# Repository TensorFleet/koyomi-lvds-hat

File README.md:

# Project Koyomi - display testing hat

This is the first part of the development of Project Koyomi, read [this blog post](https://blog.exentio.sexy/2023/12/11/project-koyomi-planning.html)
for more.  
The purpose of this Raspberry Pi hat is to test and play around with the
display of the Vaio P before further development of the motherboard.  

The board is currently tested and working [as shown here](https://blog.exentio.sexy/2024/05/09/project-koyomi-update-3.html)!

The board uses Texas Instruments' SN75LVDS83B LVDS transmitter using the Pi's
DPI signals to send video out to the display. The final motherboard will use a
DVI receiver to free up the Raspberry's GPIO, a small converter board is in
development and [you can find it here](https://github.com/exentio/koyomi-hdmi-lvds).  

The display connector is made by I-PEX, and the model numbers are
`20374-030E-31`/`20374-R30E-31`, they're the same but the 0 variant seems to be
more common.  
The display, in my case a LT080EE04100 by Toshiba (it should be the same for
all Vaio Ps), has no backlight driver, and for that the backlight pins are
broken out, allowing testing of different drivers.  
The driver will be controlled using software I2C since all the hardware I2C
pins are already used by DPI. The assigned GPIOs are 23 for SDA and 24 for SCL.
More info about software I2C on [this page](https://learn.adafruit.com/raspberry-pi-i2c-clock-stretching-fixes/software-i2c).

The current settings used in `config.txt` (on top of the default) is:  
```
dtparam=i2c_arm=off
dtparam=spi=off
display_auto_detect=0
dtoverlay=vc4-kms-dpi-generic
dtparam=hactive=1600,hfp=32,hsync=65,hbp=97
dtparam=vactive=768,vfp=1,vsync=1,vbp=8
dtparam=width-mm=182,height-mm=87
dtparam=clock-frequency=83600000,rgb666
framebuffer_width=1600
framebuffer_height=768
dtoverlay=i2c-gpio,i2c_gpio_sda=23,i2c_gpio_scl=24
disable_overscan=1
```
---

Huge thanks to Arya ([@CRImier](https://github.com/CRImier)) for her help during most phases of the design!

---

## Note on this copy (TensorFleet)

This is a **modified copy** of [exentio/koyomi-lvds-hat](https://github.com/exentio/koyomi-lvds-hat),
redistributed under CERN-OHL-S-2.0. It exists because GitHub would not let us fork the upstream
repository (`403: You can't fork this repository at this time`), so we could not open a pull request.

**Modification made** (CERN-OHL-S-2.0 §3.3 requires modifications to be identified):

- `Add F.Mask to DLP2ADN121HL4L pads so FL1/FL2 are solderable` — the
  `Murata_DLP2ADN121HL4L` footprint declared its pads as `(layers "F.Cu" "F.Paste")` with no
  `"F.Mask"`, so no solder mask openings were generated for FL1/FL2 and all 16 pads were covered by
  solder mask. Fixed in the library footprint and in both placed instances. Exporting the F.Mask layer
  before and after gives 197 → 213 flashes: exactly 16 new openings, all at the FL1/FL2 pad
  coordinates, nothing else changed.

  Found when JLCPCB flagged it during production-file preparation for a batch of these boards. Note
  that KiCad's DRC does **not** check for missing solder mask openings, so this passes a clean DRC.

Everything else is unmodified upstream work by Exentio. `gerbers/` is upstream's snapshot and has
**not** been regenerated, so it still reflects the pre-fix state — regenerate from source before
fabricating.

Upstream author: if you're reading this, the fix is a two-line change and we'd happily send it as a PR
if forking becomes possible. Thanks for publishing the design.

## TensorFleet compact RGB variant

`variants/koyomi-lvds-hat-rgb-compact-r2.0/` is a fabrication-closed compact
fork of the tested RGB/DPI design. It replaces the 2×20 Raspberry Pi header
with the carrier's 40-contact FH41 FFC, consolidates the system connection into
one harness, and demonstrates a 65.0 × 28.25 mm half-area floorplan. See the
variant README for its exact status and routing gate.

`variants/koyomi-lvds-hat-rgb-compact-r2.1-single-side/` preserves that outline
and interface while moving every fitted SMD component to the front. It is the
single-side-assembly successor and remains fabrication-closed until routing and
release verification are complete.

`variants/koyomi-lvds-hat-rgb-compact-r2.2-backlight-ffc/` adds one keyed
12-contact FFC connector for the complete legacy J5/J6 LCD-backlight harness:
VCD1–VCD6, VAD, 5 V, ground, PWM, enable, and the preserved unused contact.
It remains a single-side, half-area floorplan and is still fabrication-closed
pending native routing and release verification.

`variants/koyomi-lvds-hat-rgb-compact-r2.6-production/` is the current compact
RGB fabrication candidate. It is fully routed, keeps all 23 fitted parts on the
top side, passes zero-error DRC/ERC and the routed interface audit, and restores
all panel-sideband and backlight endpoints through the consolidated cables. It
must be paired with CM5 carrier B2.2; see the variant README and the checksumed
`fab/r2.6-compact-rgb-production-jlc-candidate/` package before quoting.

`variants/koyomi-lvds-hat-rgb-compact-r2.7-30pct-floorplan/` is the immutable,
fully routed 58.0 × 22.2 mm-base successor. It reduces R2.6 PCB area by 29.33%,
retains all 23 fitted parts on the top side, and passes DRC, ERC, routed-interface,
interconnect, and edge-orientation release gates.

`variants/koyomi-lvds-hat-rgb-compact-r2.8-c91592/` preserves the complete R2.7
geometry and routing while changing FL1/FL2 to the in-stock Murata
`DLP2ADN900HL4L` / JLCPCB `C91592` substitution previously fitted by JLCPCB.
Its checksumed manufacturing package is
`fab/r2.8-compact-rgb-production-jlc-c91592/`.

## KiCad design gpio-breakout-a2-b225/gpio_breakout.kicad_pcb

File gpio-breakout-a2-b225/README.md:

# GPIO LCD bench adapter A2 — B2.25 numbered interface

This Raspberry Pi GPIO addon drives the separately updated LCD/Combined
peripheral C1 board. It preserves A1 in `../gpio-breakout`. Its 40-contact Samtec
interface follows the corrected B2.25 allocation; historical Hirose LCD boards
are incompatible.

**Qualification corrections implemented; not fabrication released.** The saved
JLC stackup, power widths, J1 paste, USB contact routing and startup circuit are
corrected. Six Pi-side display resistor arrays provide tuning options. Native
DRC has **0 errors/0 opens** and ERC has **0 active errors**. Hardware USB/power,
display and installed cable qualification remain open. See the
[current review and exact source hashes](reports/qualification-fixes.md) and
[bench procedure](reports/bench-qualification-plan.md).

## Interface and use

J1 is **Samtec ZF5S-40-01-T-WT-K-TR/C3169111**. USB uses VBUS pins 1–4,
D−6 and D+7; grounds are 5/8. LCD power and GPIO use pins 9–40. All 40 numbered
functions are preserved. [Pinout](interface-pinout.csv) lists physical Pi header
pins and the updated power/series-element paths. The native comparison is in
[interface-audit.json](reports/interface-audit.json).

J3 is **Molex 1054500101/C134092**. Connect a normal USB-A-to-C cable from the Pi
host port; the GPIO header itself does not carry USB. This is USB2 pass-through
with protection, not a hub. Both CC contacts have independent 5.1 kΩ pulldowns.
TPD2EUSB30 arrays protect data and CC; no whole-board ESD compliance is claimed.

RN1–RN6 insert one isolated **0 Ω** element on each of GPIO0–21, with GPIO0/1
named ID_SD/ID_SC. Their six four-element arrays are `4D03WGJ0000T5E/C1952`.
Select nonzero source values only after confirming the Pi/display timing and
coordinating C1's receiver-side resistor banks. Software must select the
corresponding alternate functions and display mode.

## Power and assembly

- Scope is **low-power USB2 bench use**. Full downstream USB-A load capacity
  is not provided. The 0.5 A PTC is not a precise current limit.
- USB VBUS passes through F2, TPS22918DBVR/C131941 and the existing LM66100
  reverse blocker. A 10 nF CT capacitor targets a typical 26.55 ms 10–90% rise
  at 5 V. QOD is unconnected. Actual startup current, host droop and load voltage
  still require measurements; this circuit does not implement USB enumeration.
- **JP4 (5 V) and JP5 (3.3 V) default OPEN.** Close only when the Pi is the sole
  source of those LCD supplies. Keep open for independently powered LCD
  electronics; closed links are not automatic reverse-current protection.
  JP4 includes F1, the retained 0.5 A PTC. USB supply remains separate.
- J2 is a hand-fit 2×20 Pi header/stacking socket. No particular stacking socket
  or Pi mechanical fit has been qualified. Pin 1 is marked. TP4/GND and
  TP5/Pi3V3 remain.
- J1's 42 pads include paste. C1's latest J401 also has 42 paste-enabled pads;
  the earlier peer paste finding is closed. Stencil and exact-part sourcing
  belong in the eventual gated fabrication package.

## Verification and limits

The 63.5×32 mm board has 27 footprints. All 193 numbered pads match the native
schematic XML and all 40 interface functions match. Native DRC retains 13
library snapshot warnings; ERC retains 25 library snapshot differences and
four intentionally unused Pi GPIO label warnings. The previous exact
TI-documented ST-to-ground exclusion remains; no global rule was weakened.

The saved four-layer JLC04161H-7628 construction is verified. Main USB pair
width/gap remains 0.2774/0.20 mm; minimum track width is 0.20 mm, ordinary via
drills are 0.30 mm. B6/B7 planar branches shortened to 1.588/4.312 mm, but B7
has two transitions while B6 has none. Coplanar ground is interrupted. These
geometry results do not qualify uniform impedance or the assembled channel.

[Current top](renders/qualification-fixes-top.png),
[USB-entry side](renders/qualification-fixes-right.png) and
[native schematic](renders/schematic/gpio_breakout.svg) reflect the final sources.
J1 is still a nominal envelope, not detailed Samtec CAD. J2 has no chosen socket
model. J3 uses the unmodified official Molex STEP with its mouth facing outward
at X113.55 mm, 0.05 mm past the board edge; plug-shroud clearance needs checking.

The catalog cable candidate is
[Samtec FJH-40-R-03.00-4](https://www.samtec.com/products/fjh-40-r-03.00-4),
76.2 mm. Both connectors match its manufacturer mating family, but installed
contact faces, pin-one arrangement, length and latch/fold clearance remain
unverified. Custom harnesses and repinning are prohibited. Physical continuity
is a TODO after cable selection and is not the sole release blocker.

## Reproduction and release

All native edits and checks are instrumented. Sources, current reports and
renders are hash-bound in the telemetry artifact manifest. Tools under `tools/`
are audited sequential revision steps, not a single idempotent generator.
Do not rerun historical netlist import/routing on the completed board. Use the
pinned September 5 KiCad CLI through `KICAD_CLI`; see
[the runtime record](reports/runtime-and-review.md). No shared installation was
modified. Standard package models were copied into project-relative paths.

The authoritative `gpio-breakout-a2` contract in
[private interconnect PR34](https://github.com/TensorFleet/vaio_p_modding/pull/34)
retains the hardware and installed-cable qualification hold. No Gerbers, drill,
BOM, CPL or JLC upload were produced during these corrections. Before any
fabrication generation, run `scripts/check_interconnect_release.py --board
gpio-breakout-a2` in that repository; it must pass. Older reports are historical
when their source hashes differ from the current review.

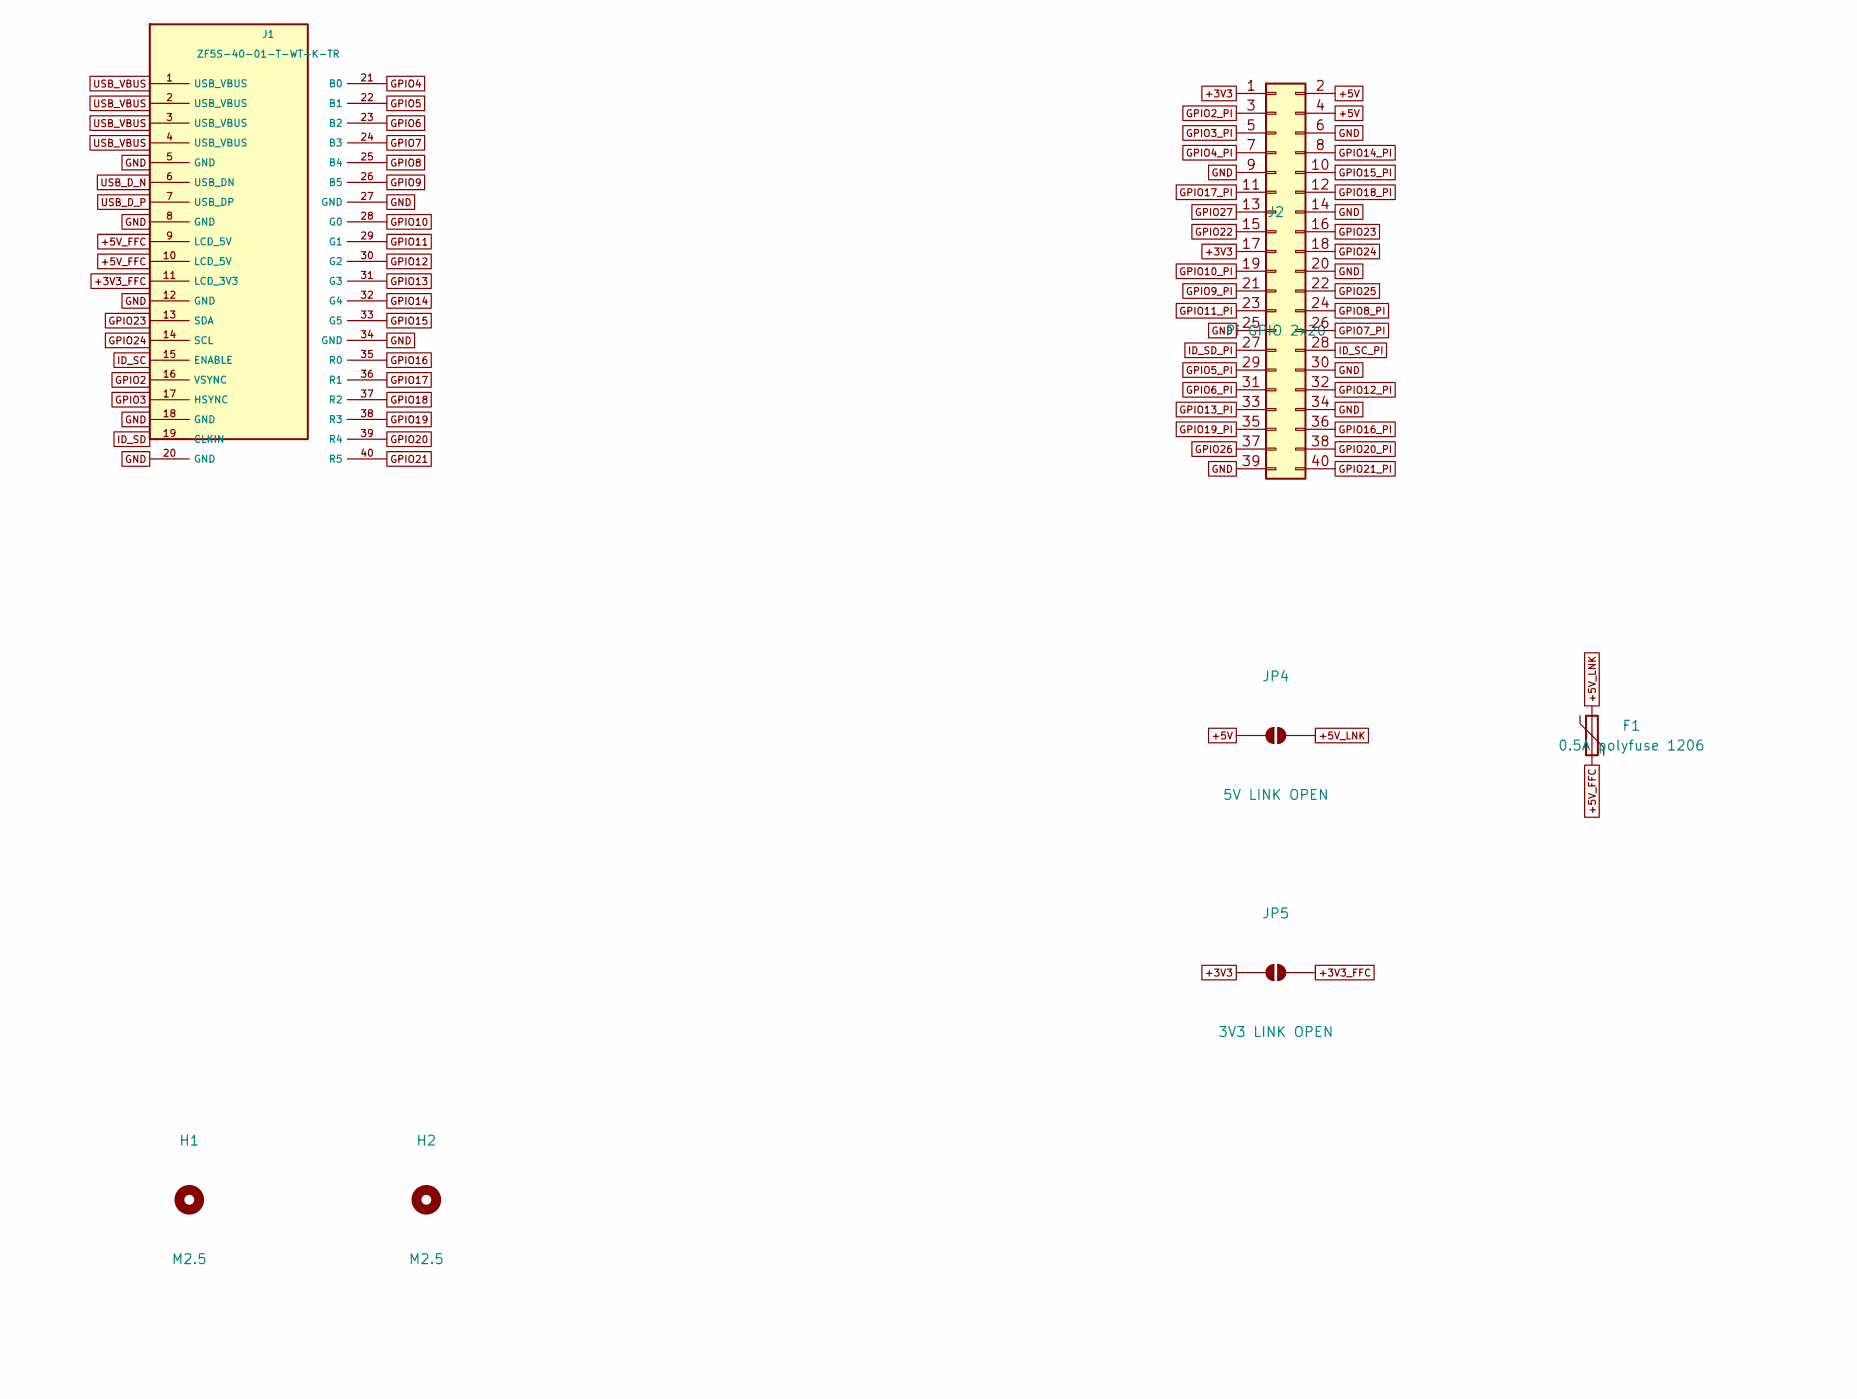
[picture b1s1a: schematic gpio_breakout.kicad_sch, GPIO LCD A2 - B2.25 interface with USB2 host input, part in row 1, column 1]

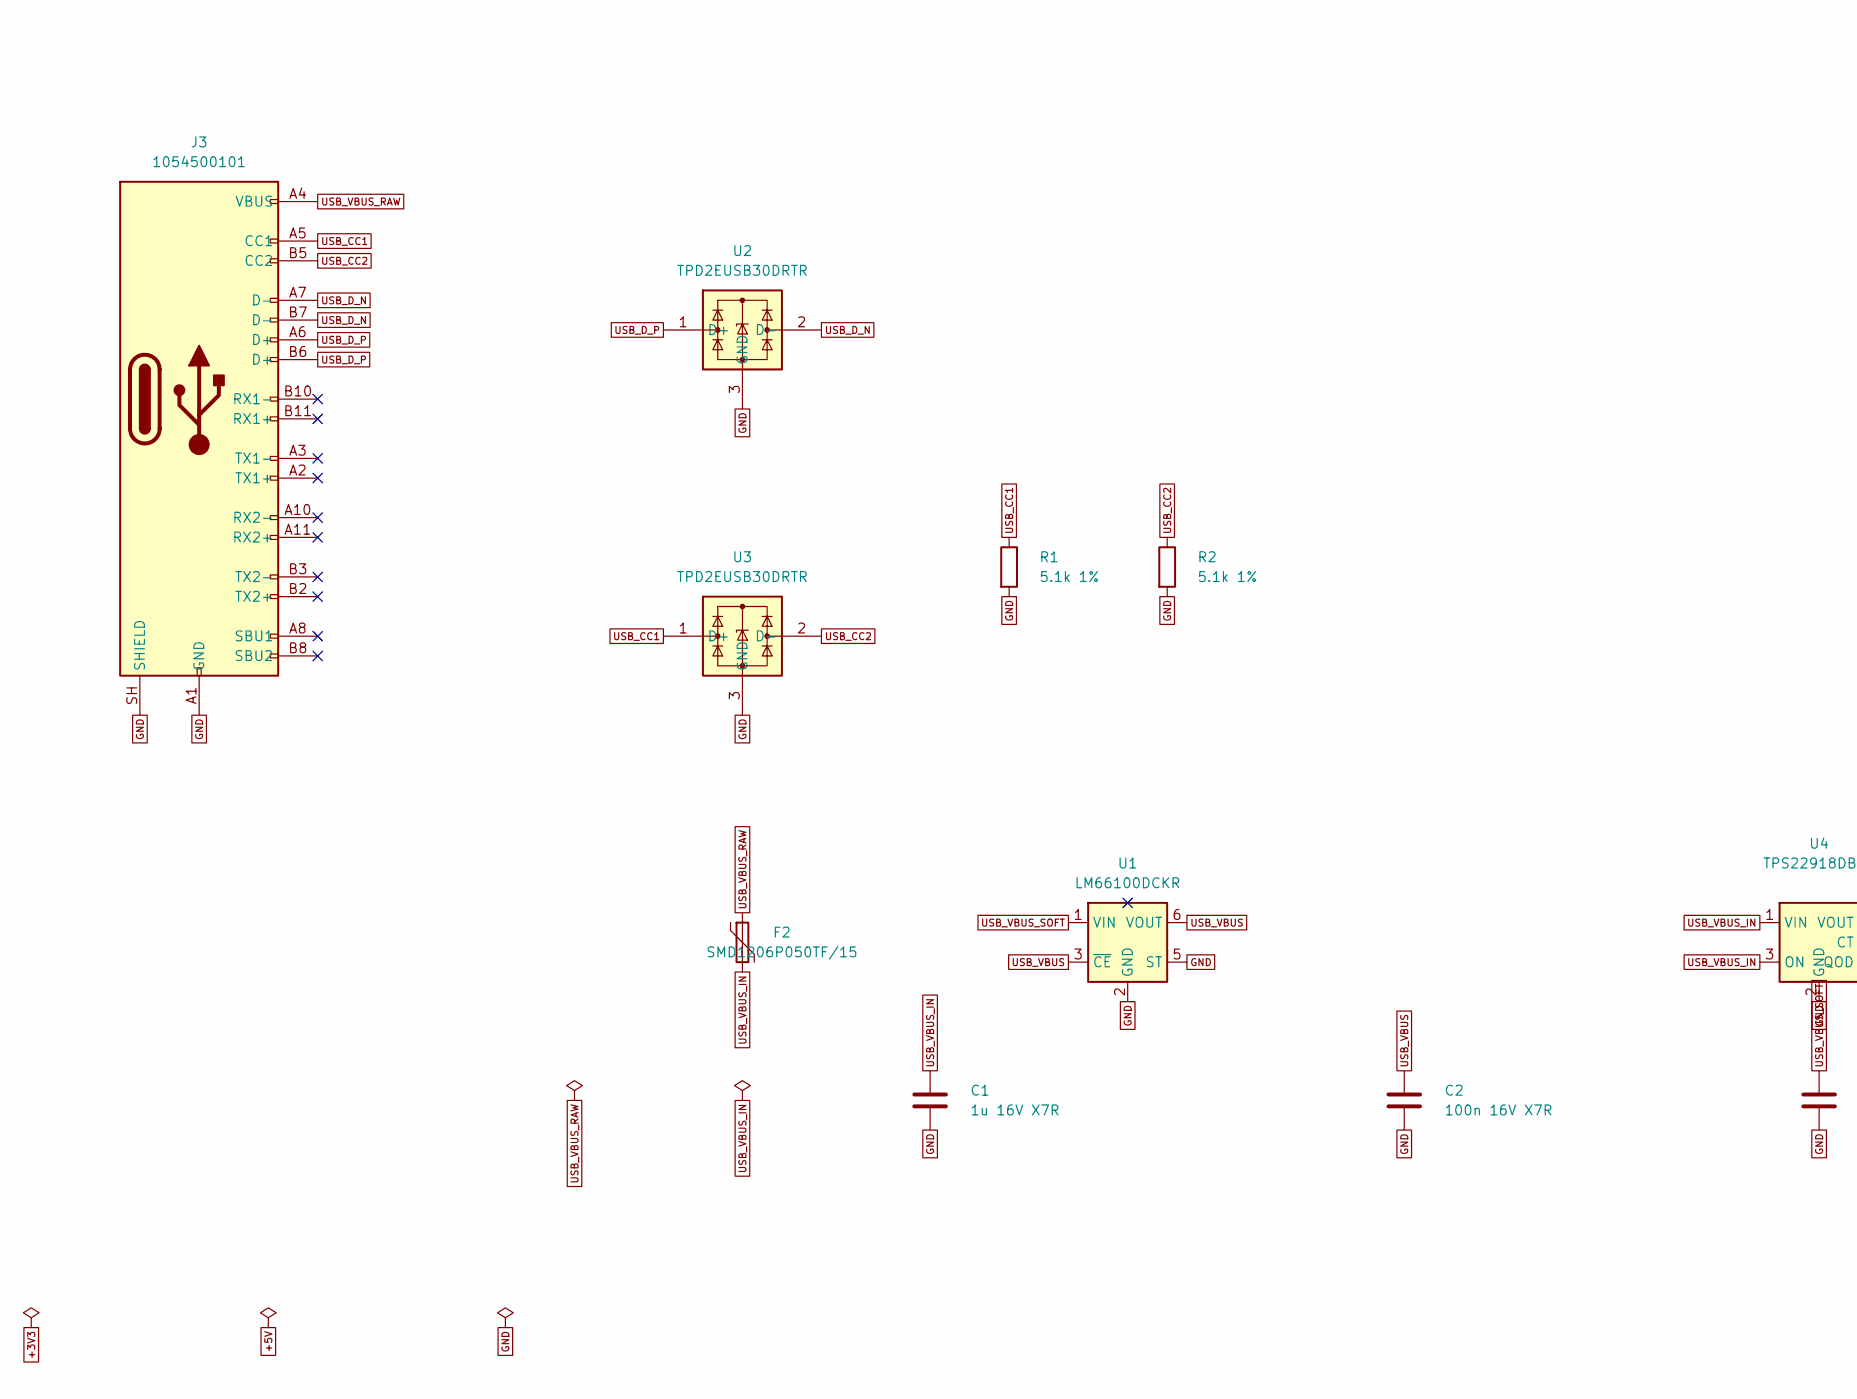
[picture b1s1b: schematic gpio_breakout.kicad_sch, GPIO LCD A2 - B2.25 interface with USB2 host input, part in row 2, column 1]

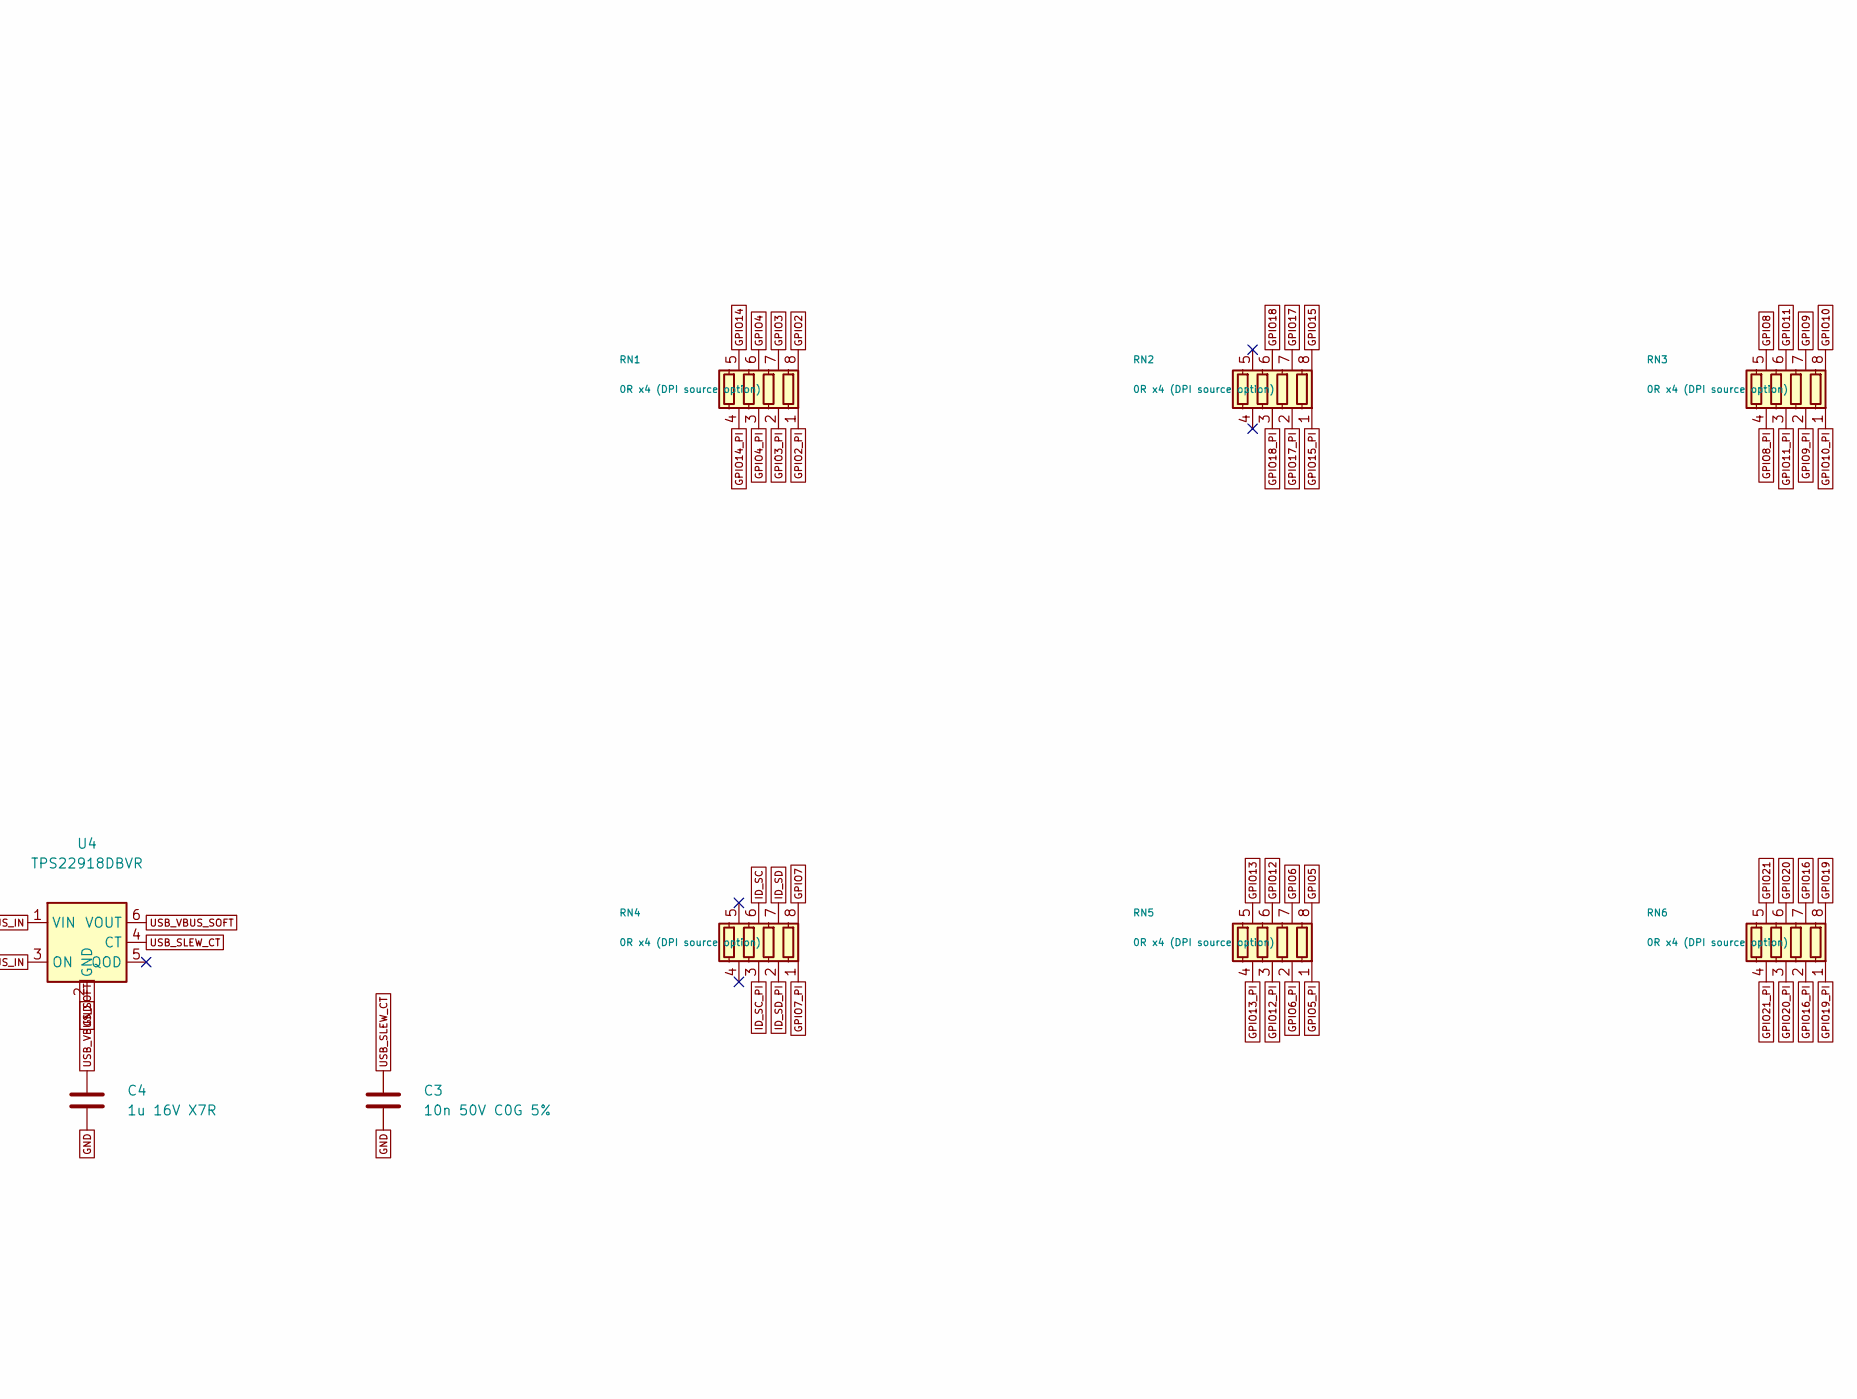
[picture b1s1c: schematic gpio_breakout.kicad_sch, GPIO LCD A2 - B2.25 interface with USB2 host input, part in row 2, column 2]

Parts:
C1, C4: 1u 16V X7R; C_0603_1608Metric
C2: 100n 16V X7R; C_0603_1608Metric
C3: 10n 50V C0G 5%; C_0603_1608Metric; MPN C1608C0G1H103JT000N; LCSC C76599
F1: 0.5A polyfuse 1206; Fuse_1206_3216Metric
F2: SMD1206P050TF/15; Fuse_1206_3216Metric
H1, H2: M2.5; MountingHole_2.7mm_M2.5
J1: ZF5S-40-01-T-WT-K-TR; Samtec_ZF5S-40-01-T-WT_1x40_P0.50mm; LCSC C3169111
J2: Pi GPIO 2x20; PinHeader_2x20_P2.54mm_Vertical
J3: 1054500101; USB_C_Receptacle_Molex_105450-0101
JP4: 5V LINK OPEN; SolderJumper-2_P1.3mm_Open_RoundedPad1.0x1.5mm
JP5: 3V3 LINK OPEN; SolderJumper-2_P1.3mm_Open_RoundedPad1.0x1.5mm
R1, R2: 5.1k 1%; R_0603_1608Metric
RN1, RN2, RN3, RN4, RN5, RN6: 0R x4 (DPI source option); R_Array_Convex_4x0603; MPN 4D03WGJ0000T5E; LCSC C1952
TP4: GND; TestPoint_Pad_1.5x1.5mm
TP5: 3V3; TestPoint_Pad_1.5x1.5mm
U1: LM66100DCKR; SOT-363_SC-70-6
U2, U3: TPD2EUSB30DRTR; Texas_DRT-3
U4: TPS22918DBVR; SOT-23-6; MPN TPS22918DBVR; LCSC C131941

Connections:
+3V3: J2.1, J2.17, JP5.1 (A), TP5.1 (1_1)
+3V3_FFC: J1.11 (LCD_3V3), JP5.2 (B)
+5V: J2.2, J2.4, JP4.1 (A)
+5V_FFC: F1.2, J1.9 (LCD_5V), J1.10 (LCD_5V)
+5V_LNK: F1.1, JP4.2 (B)
GND: C1.2, C2.2, C3.2, C4.2, J1.5 (GND), J1.8 (GND), J1.12 (GND), J1.18 (GND), J1.20 (GND), J1.27 (GND), J1.34 (GND), J2.6, J2.9, J2.14, J2.20, J2.25, J2.30, J2.34, J2.39, J3.A1 (GND), J3.A12 (GND), J3.B1 (GND), J3.B12 (GND), J3.SH (SHIELD), R1.2, R2.2, TP4.1 (1_1), U1.2 (GND), U1.5 (ST), U2.3 (GND), U3.3 (GND), U4.2 (GND)
GPIO2: J1.16 (VSYNC), RN1.8 (R1.2)
GPIO2_PI: J2.3, RN1.1 (R1.1)
GPIO3: J1.17 (HSYNC), RN1.7 (R2.2)
GPIO3_PI: J2.5, RN1.2 (R2.1)
GPIO4: J1.21 (B0), RN1.6 (R3.2)
GPIO4_PI: J2.7, RN1.3 (R3.1)
GPIO5: J1.22 (B1), RN5.8 (R1.2)
GPIO5_PI: J2.29, RN5.1 (R1.1)
GPIO6: J1.23 (B2), RN5.7 (R2.2)
GPIO6_PI: J2.31, RN5.2 (R2.1)
GPIO7: J1.24 (B3), RN4.8 (R1.2)
GPIO7_PI: J2.26, RN4.1 (R1.1)
GPIO8: J1.25 (B4), RN3.5 (R4.2)
GPIO8_PI: J2.24, RN3.4 (R4.1)
GPIO9: J1.26 (B5), RN3.7 (R2.2)
GPIO9_PI: J2.21, RN3.2 (R2.1)
GPIO10: J1.28 (G0), RN3.8 (R1.2)
GPIO10_PI: J2.19, RN3.1 (R1.1)
GPIO11: J1.29 (G1), RN3.6 (R3.2)
GPIO11_PI: J2.23, RN3.3 (R3.1)
GPIO12: J1.30 (G2), RN5.6 (R3.2)
GPIO12_PI: J2.32, RN5.3 (R3.1)
GPIO13: J1.31 (G3), RN5.5 (R4.2)
GPIO13_PI: J2.33, RN5.4 (R4.1)
GPIO14: J1.32 (G4), RN1.5 (R4.2)
GPIO14_PI: J2.8, RN1.4 (R4.1)
GPIO15: J1.33 (G5), RN2.8 (R1.2)
GPIO15_PI: J2.10, RN2.1 (R1.1)
GPIO16: J1.35 (R0), RN6.7 (R2.2)
GPIO16_PI: J2.36, RN6.2 (R2.1)
GPIO17: J1.36 (R1), RN2.7 (R2.2)
GPIO17_PI: J2.11, RN2.2 (R2.1)
GPIO18: J1.37 (R2), RN2.6 (R3.2)
GPIO18_PI: J2.12, RN2.3 (R3.1)
GPIO19: J1.38 (R3), RN6.8 (R1.2)
GPIO19_PI: J2.35, RN6.1 (R1.1)
GPIO20: J1.39 (R4), RN6.6 (R3.2)
GPIO20_PI: J2.38, RN6.3 (R3.1)
GPIO21: J1.40 (R5), RN6.5 (R4.2)
GPIO21_PI: J2.40, RN6.4 (R4.1)
GPIO22: J2.15
GPIO23: J1.13 (SDA), J2.16
GPIO24: J1.14 (SCL), J2.18
GPIO25: J2.22
GPIO26: J2.37
GPIO27: J2.13
ID_SC: J1.15 (ENABLE), RN4.6 (R3.2)
ID_SC_PI: J2.28, RN4.3 (R3.1)
ID_SD: J1.19 (CLKIN), RN4.7 (R2.2)
ID_SD_PI: J2.27, RN4.2 (R2.1)
USB_CC1: J3.A5 (CC1), R1.1, U3.1 (D+)
USB_CC2: J3.B5 (CC2), R2.1, U3.2 (D-)
USB_D_N: J1.6 (USB_DN), J3.A7 (D-), J3.B7 (D-), U2.2 (D-)
USB_D_P: J1.7 (USB_DP), J3.A6 (D+), J3.B6 (D+), U2.1 (D+)
USB_SLEW_CT: C3.1, U4.4 (CT)
USB_VBUS: C2.1, J1.1 (USB_VBUS), J1.2 (USB_VBUS), J1.3 (USB_VBUS), J1.4 (USB_VBUS), U1.3 (~CE), U1.6 (VOUT)
USB_VBUS_IN: C1.1, F2.2, U4.1 (VIN), U4.3 (ON)
USB_VBUS_RAW: F2.1, J3.A4 (VBUS), J3.A9 (VBUS), J3.B4 (VBUS), J3.B9 (VBUS)
USB_VBUS_SOFT: C4.1, U1.1 (VIN), U4.6 (VOUT)

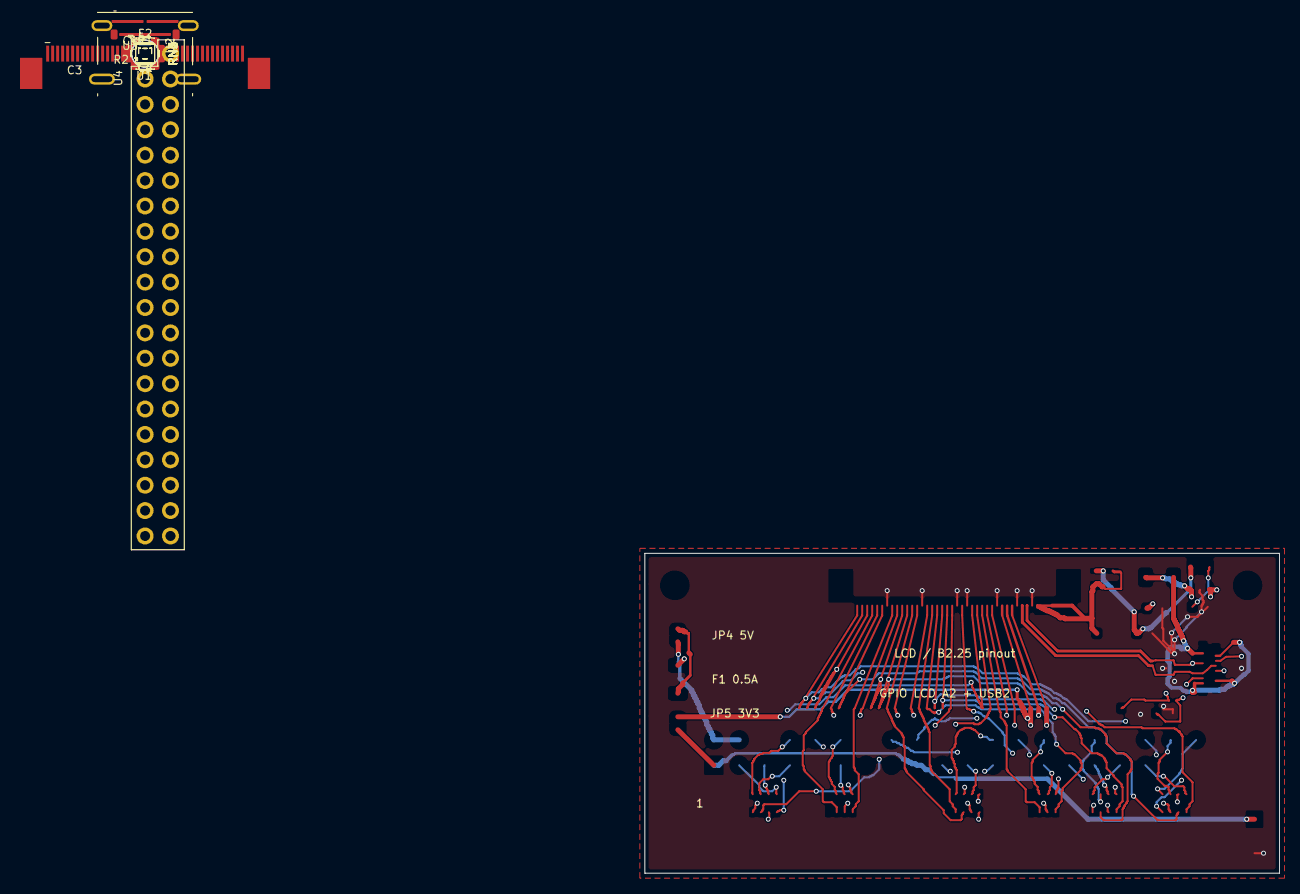
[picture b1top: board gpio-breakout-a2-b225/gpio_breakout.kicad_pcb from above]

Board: 4 copper layers, 63.5 x 32.0 mm, 27 parts (0 on the bottom side), 61 nets.

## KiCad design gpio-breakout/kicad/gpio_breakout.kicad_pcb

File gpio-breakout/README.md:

# koyomi gpio-breakout A1 — 40-pin FFC to Pi GPIO bench adapter

Bench adapter: the carrier/LCD system's 40-contact FFC (Hirose
FH41-40S-0.5SH(05), C596805 — the JDISP1/JFFC1 interconnect) broken out 1:1 to
a standard Raspberry Pi 40-pin 2.54 mm header, so a stock Pi can drive the
Koyomi LVDS chain over the production FFC, or probe a carrier's display FFC.

**A1 addresses the 2026-08-20 A0 design review**: 63.5 × 32 mm, **4-layer**
(F sig / In1 solid GND plane / In2 GND pour / B sig+pour), corrected FH41
land pattern (0.30 × 0.65 copper, 0.25 paste via paste-margin), fused and
cuttable power links, all connector pins connected (pads 41–50 shield → GND),
FH41 symbol pins retyped passive.

## Gates (this commit, reproducible)

- Errors-only ERC: 0. Errors-only DRC: **0 violations, 0 unconnected, 0
  footprint errors** (`kicad/drc-errors.rpt`).
- All-severity DRC: 30 cosmetic silkscreen warnings, **zero dangling copper**
  (`kicad/drc-all.rpt`). All-severity ERC: 31 library-snapshot notices
  (`kicad/erc-all.rpt`) — recorded, not waived.
- NOT fabrication-released: the interconnect contract entry (registered in
  vaio_p_modding) pins the cable question — FH41 is specified for shielded
  0.3 mm FFC with ground contacts; an exact shielded cable P/N (or a reviewed
  decision to accept unshielded AWM 20624 for bench-only use) is required
  before Gerber/BOM/CPL generation.

## Power (new in A1)

Pi → FFC power is **fused and severable**:

- `JP4` (5V LINK) and `JP5` (3V3 LINK): solder jumpers, **bridged by default**
  so the adapter works out of the box; **cut them when the LCD chain is
  powered externally** (backside silk says so) to prevent backfeeding the Pi.
- `F1`: 0.5 A PTC polyfuse (1206) in the 5 V path — matches the FH41 0.5 A
  contact rating. Budget: serializer ≈50 mA on 3V3; backlight loads belong on
  a separate supply, not through this adapter.

## The three special pins — jumpers OPEN by default

FFC 17/34/39 are PANEL_ID0/PANEL_ID1/LCD_INS in the FFC system but 3V3/GND/GND
on a real Pi. They are isolated behind default-OPEN solder jumpers JP1–JP3
with test pads TP1–TP3 (TP4 GND, TP5 3V3 alongside). Close JP1/JP2 to strap
IDs, JP3 to report "panel inserted". Open = safe, and correct for the
retrofit (straps ignored, WP-003e).

## Assembly definition

- **J1 (FH41, C596805): JLC SMT-placed** — the only machine-placed part
  besides F1/JP jumper pads.
- **J2: DNP for assembly — hand-fit.** For riding a Pi, solder a 2×20
  **stacking socket** from the BOTTOM face (exact P/N to be pinned at order
  time); for cable use, a plain 2×20 pin header on top. Pin 1 = square pad,
  marked `1` on silk.
- FFC contacts face DOWN (silk marked) — same bottom-contact convention and
  cable fold rules as the carrier↔LCD link.

Generated headlessly (tools/: netlist_def_bo, gen_sch_bo, gen_pcb_bo,
route_board + pre-lay scripts); Freerouting 2.2.4 jar SHA-256 verified. GND
mid-row pads are stitched to the In1 plane with dedicated vias; power runs are
hand-placed locked copper laid before autorouting.

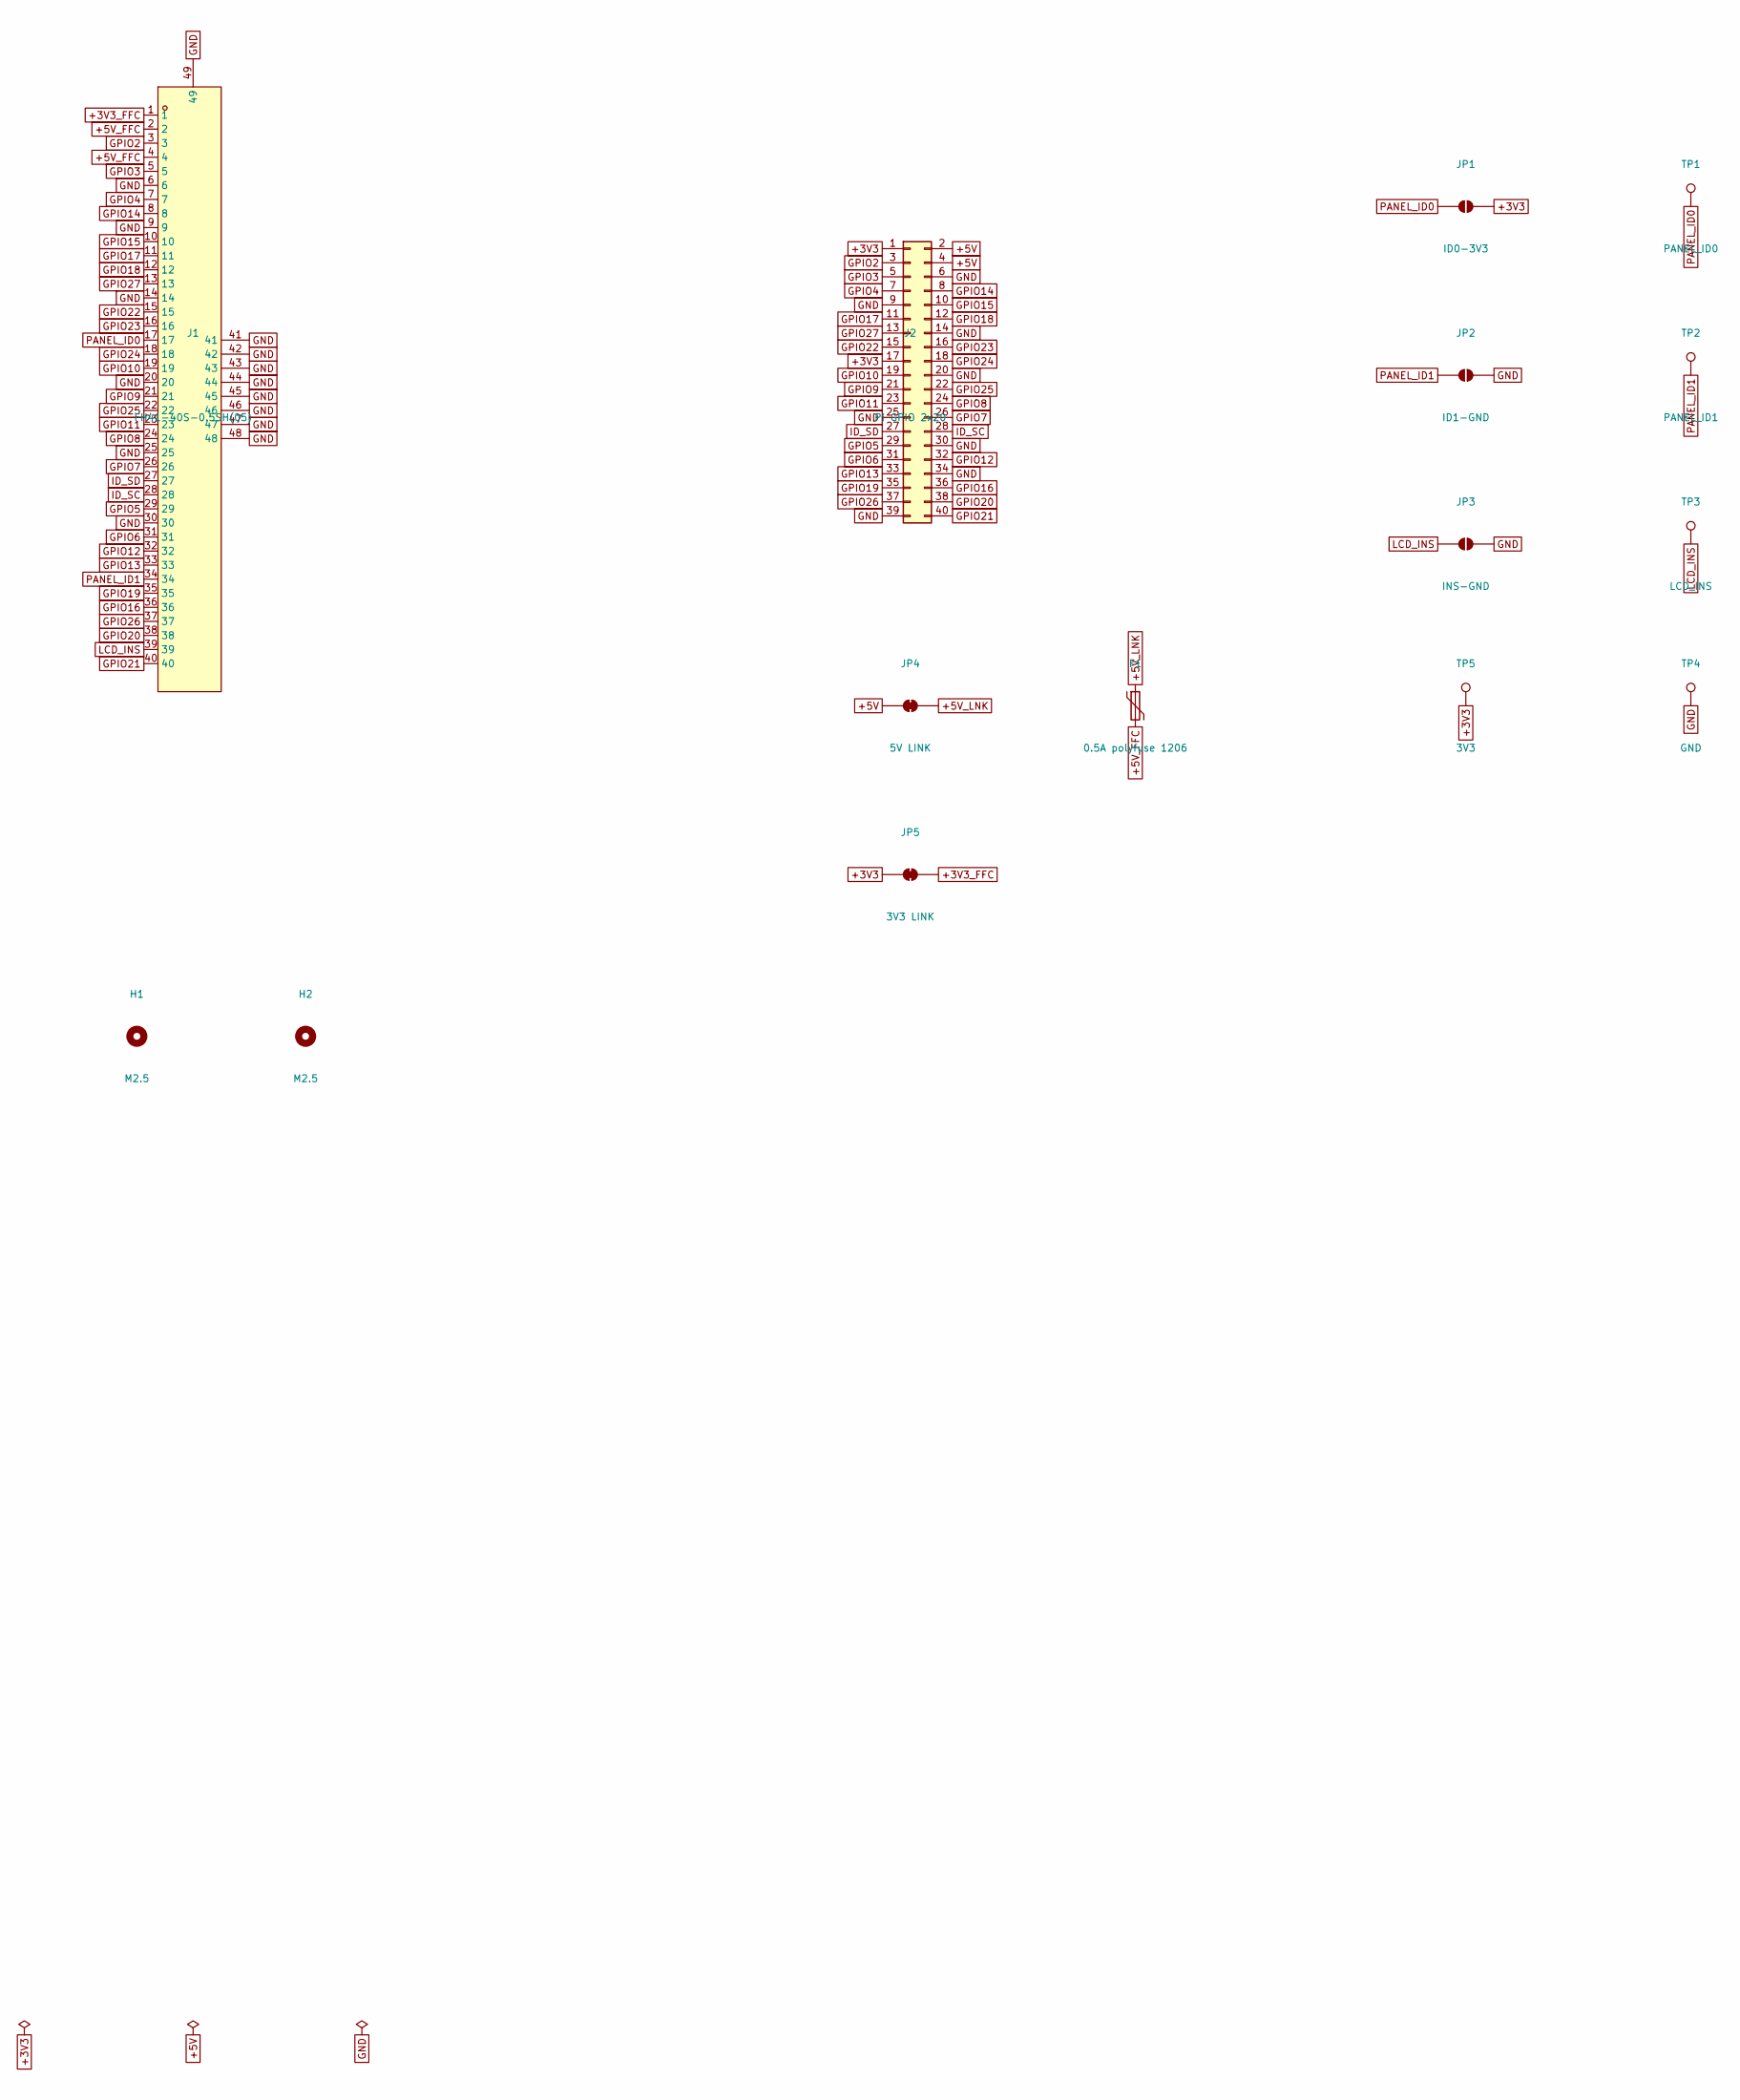
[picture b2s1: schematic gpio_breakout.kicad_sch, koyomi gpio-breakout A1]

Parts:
F1: 0.5A polyfuse 1206; Fuse_1206_3216Metric
H1, H2: M2.5; MountingHole_2.7mm_M2.5
J1: FH41-40S-0.5SH(05); FPC-SMD_FH41-40S-0.5SH; LCSC C596805
J2: Pi GPIO 2x20; PinHeader_2x20_P2.54mm_Vertical
JP1: ID0-3V3; SolderJumper-2_P1.3mm_Open_RoundedPad1.0x1.5mm
JP2: ID1-GND; SolderJumper-2_P1.3mm_Open_RoundedPad1.0x1.5mm
JP3: INS-GND; SolderJumper-2_P1.3mm_Open_RoundedPad1.0x1.5mm
JP4: 5V LINK; SolderJumper-2_P1.3mm_Bridged_RoundedPad1.0x1.5mm
JP5: 3V3 LINK; SolderJumper-2_P1.3mm_Bridged_RoundedPad1.0x1.5mm
TP1: PANEL_ID0; TestPoint_Pad_1.5x1.5mm
TP2: PANEL_ID1; TestPoint_Pad_1.5x1.5mm
TP3: LCD_INS; TestPoint_Pad_1.5x1.5mm
TP4: GND; TestPoint_Pad_1.5x1.5mm
TP5: 3V3; TestPoint_Pad_1.5x1.5mm

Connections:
+3V3: J2.1, J2.17, JP1.2 (B), JP5.1 (A), TP5.1
+3V3_FFC: J1.1, JP5.2 (B)
+5V: J2.2, J2.4, JP4.1 (A)
+5V_FFC: F1.2, J1.2, J1.4
+5V_LNK: F1.1, JP4.2 (B)
GND: J1.6, J1.9, J1.14, J1.20, J1.25, J1.30, J1.41, J1.42, J1.43, J1.44, J1.45, J1.46, J1.47, J1.48, J1.49, J1.50, J2.6, J2.9, J2.14, J2.20, J2.25, J2.30, J2.34, J2.39, JP2.2 (B), JP3.2 (B), TP4.1
GPIO2: J1.3, J2.3
GPIO3: J1.5, J2.5
GPIO4: J1.7, J2.7
GPIO5: J1.29, J2.29
GPIO6: J1.31, J2.31
GPIO7: J1.26, J2.26
GPIO8: J1.24, J2.24
GPIO9: J1.21, J2.21
GPIO10: J1.19, J2.19
GPIO11: J1.23, J2.23
GPIO12: J1.32, J2.32
GPIO13: J1.33, J2.33
GPIO14: J1.8, J2.8
GPIO15: J1.10, J2.10
GPIO16: J1.36, J2.36
GPIO17: J1.11, J2.11
GPIO18: J1.12, J2.12
GPIO19: J1.35, J2.35
GPIO20: J1.38, J2.38
GPIO21: J1.40, J2.40
GPIO22: J1.15, J2.15
GPIO23: J1.16, J2.16
GPIO24: J1.18, J2.18
GPIO25: J1.22, J2.22
GPIO26: J1.37, J2.37
GPIO27: J1.13, J2.13
ID_SC: J1.28, J2.28
ID_SD: J1.27, J2.27
LCD_INS: J1.39, JP3.1 (A), TP3.1
PANEL_ID0: J1.17, JP1.1 (A), TP1.1
PANEL_ID1: J1.34, JP2.1 (A), TP2.1

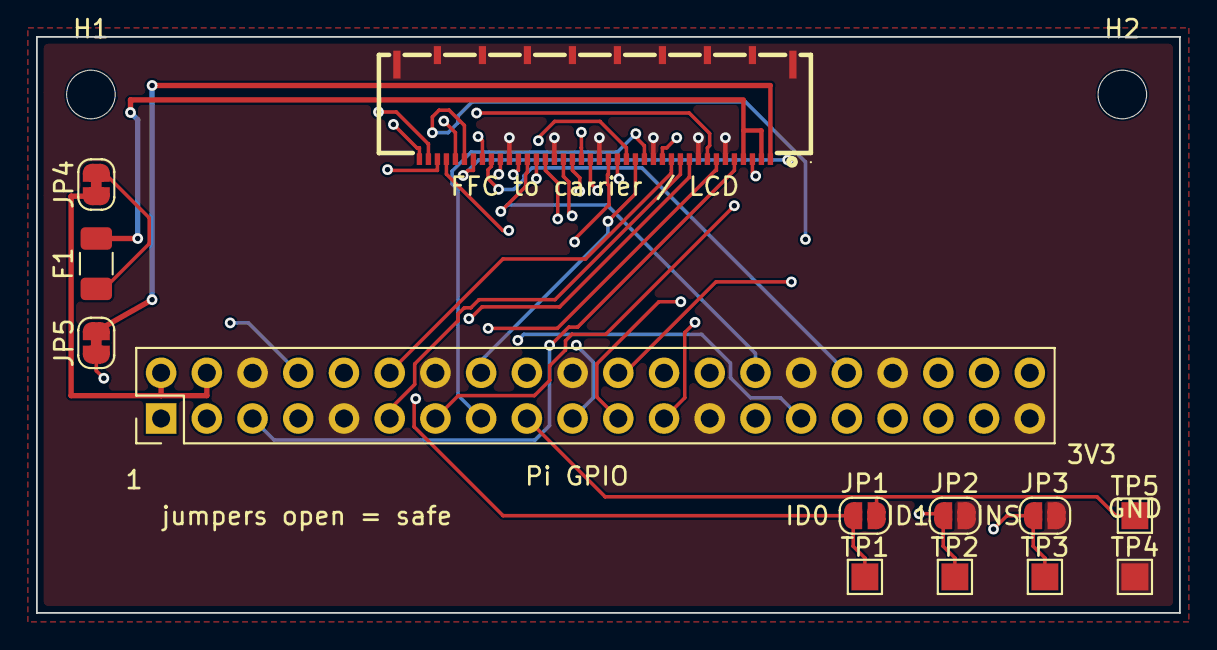
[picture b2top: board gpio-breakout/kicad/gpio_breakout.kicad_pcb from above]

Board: 4 copper layers, 63.5 x 32.0 mm, 15 parts (0 on the bottom side), 37 nets.
